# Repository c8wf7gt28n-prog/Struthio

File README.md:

# Graphite 0.8.3 · Kasandra's hologram, her typewriter face for every word, DELETE, burnt yellow and the neon kp

Graphite is a quiet workspace for ideas, research, documents and engineering work, with its AI beside the work. It runs on
one minimal Debian computer (a phone is optional access) and keeps everything on that computer unless you turn a service
on. Graphite is the public name of the workspace; its assistant's face is Stacy (Kasandra in the Kasandra appearance); before November 6, 2026 the program was called Ledger &
Slate, and folders, scripts, settings keys and internal names keep those earlier names for compatibility.

- **From the ThinkPad** · the eight menus (Work, Revise, Tools, Arrange, Commands, Rules, Properties, Guide) stand in the open across the head; one dial sets how strongly the desk glows (Rules ▸ Desk artwork ▸ Glow: Soft, Bright, Neon; it opens on Neon); no key is printed beside the thing it does; the left trees are green circuit traces with the path to the current row lit; the menus' lines carry glyphs.
- **No System menu** · the four meters at the foot are doors: click **CPU** for Graphite's work (what runs and waits, Stop all jobs), **GPU** for Stacy's model and Graphite's services, **RAM** for memory and Machine, **TXT** for the Full chat and what Stacy has in view. Leaving (Log out, Exit Graphite, Restart, Shut down) is at the foot of the **Work** menu; the game is at the foot of **Programs**. The equalizer in the head shows everything that moves (processor, kernel, memory, disks, network, graphics); click it for what each reads. A small control at the left end of the line opens the room above it: one chevron for more, two for taller, one down to close.
- **A start in another program** · say "start a Godot project called Lander" and Stacy makes a folder in Files with the smallest project that runs (project file, one scene, one script) and a page of first steps, written for the Godot on this computer; the Godot room reads it back, and opening it in Godot is a step that waits for you, or is hers with a free hand. One Undo deletes the folder (DELETE gives it back).
- **Stacy's hand** · two words under her face (in Kasandra, on her masthead, after what she speaks with) say how far she acts by herself; click them to change it. **Ask first**: every change waits for your Approve. **Do and show** (what it opens with): a change you ask her for is made at once and shown, with one **Undo** that puts back exactly what it took. **Free hand**: she also makes the changes the records mark for approval and, after a change, brings back to current what stood on it. Say "make a folder called Bracket" or "write a file called plan.txt saying …" and it is in Files as if you had saved it, with an Undo that deletes it (DELETE gives it back). What cannot be undone always asks. Her trail (**What she did…**) lists every act.
- **One line to type on** · five names stand at the left of the line at the bottom: Stacy, Terminal, Search, Web, Log. The lit one gets the words. Web opens an address, or searches for words, in this computer's own browser; with Stacy or Search lit, a line that is only an address (https://…, www.…, localhost) is opened there too, and anything else stays with whom it was typed to. The arrow at the line's end says what it will do, and turns green to run a line that reads.
- **The head and the right pane** · the middle of the head is an equalizer: each bar is one processor thread of this computer over the last second. The right pane is one view, Stacy: her face (in Kasandra, her masthead; her picture stands as a hologram in the left pane's lower part), **This** (what is open or selected), **Now** (what is running and what waits), and the conversation.
- **Simple at rest** · the bar above the work says the name of what is open (click it for its address); tools are drawn glyphs with no boxes; Stacy is the right pane; the name of a thing is said once.
- **The map** · **Z** glides back to show the whole desk, and from that far a sheet is the glyph of its kind, its name in letters that stay readable, and the mark of its state. The Field opens as it was last seen.
- **Find, everywhere** · Find (Ctrl+F) opens one line above the work on whatever is open: writing, the cells of a sheet, a list, the lines of a finding, the words of a PDF page. Enter for the next place, Shift+Enter for the one before, Esc to close.
- **Start here** · [ThinkPad first install](docs/THINKPAD_FIRST_INSTALL.md) covers USB setup, the model-free first launch and the observed hardware.
- **Once** · each action has one visible home (its key is the second road, the right button on a thing is that thing's own road) and a name is said once. Save is lit only when a press would save something.
- **Buttons** · an action is a button (a dark plate with a quiet edge, never a bright outline) and a word that only goes somewhere is underlined, so the interface is never mistaken for the work. A PDF page is shown in the desk's light, its paper brought down from white; its own light is one line away under **More ▾**. The sheet, the PDF and the page of writing each have one row of tools, with what is needed now and then under **More ▾**; the keys at the foot of the Field are buttons.
- **Icons** · every tool is one of Graphite's own drawn glyphs with no box at all; what is particular to a page keeps its words beside its glyph. Work ▸ Rules ▸ Buttons ▸ Words brings back worded plates.
- **The mouse first** · above whatever is open in the centre: **‹ Field**, Find, **−** **+**, Undo, Redo, Save, always in the same place. In the Field **Z** shows the whole desk and the bars at the edges drag; the right button on a sheet shows what can be done with it.
- **Amber** · one amber halo marks where the keys go (the selected sheet, the page being read, or the writing line); what waits for you is lit at its mark, and Approve glows until it is pressed.
- **Green** · the pointer (the mark's two facets, aimed at 11 o'clock) is drawn in the desk's green and carries a little light over the Field; whatever it is over answers in green, and what is live glows. Amber stays for what is selected and what waits for you. The Clean desk keeps the green and drops the glow.
- **The mouse** · click a tile in the Field to open it in the centre; **‹ Field** above the centre comes back to the same tile; the buttons at the foot of the Field do what their keys do; a change that waits has an **Approve** button. Ask Stacy "set B3 to 300" and, with her hand at Do and show, it is done at once with an Undo; at Ask first it waits for your Approve with what it would move marked.
- **Every key** · press **?** in the Field for a card of every key. The doubt (X), the desk check (C) and the brief (B) open on a page over the work at your reading size; the doubt and the check step aside at the next key.
- **Look ahead** · with a sheet or a calculation selected in the Field, ask "what if B4 were 100?": the cell is set without changing anything, the wires are followed, and the Field marks everything that would move with what it would say (**Esc** clears).
- **The brief** · press **B** in the Field: the whole desk written up as one page, from the records and by no model; **G** keeps it as a page that knows when the desk has moved on.
- **Right-click** · on a sheet in the Field the menu cascades: What if › a number › a value to try; Doubt it › what Stacy finds, each row opening its evidence; Trace it › every step back and on; What can be done › the steps; Your words ›.
- **Your own words** · `word waits = field.read | pick waiting | select kind,title,state`, then `waits`, `waits | count`, `words`, `forget waits`: a line kept under a word of yours.
- **Doubt** · press **X** on a sheet in the Field: Stacy cross-examines it for what a plausible result may hide (an edited input, mixed conditions, one source, a check that cannot fail, a number recorded nowhere) and **D** offers the step that removes the doubt.
- **A line reads the desk** · `field.read | pick waiting | select kind,title,state`; `this` is the sheet selected in the Field; **T** traces a thing to its source; ask "what if B3 were 320?" about a calculation and nothing is changed.
- **Doing** · press **D** on a sheet in the Field for the steps the records offer (a read runs; a change that waits is marked "asks first" and waits for **G**, your go; with Stacy's hand at Do and show or Free hand, the others are done when you take them); **C** checks the desk and offers to settle what needs no decision of yours.
- **The shelf** · press **P** in the Field: every program and room in six fixed columns; Enter opens one.
- **The Field** · press **F9** (or Arrange → Field, or type `field` in the writing strip): the work in this workspace as sheets with the wires that say what feeds what. Arrow keys follow the wires, Enter opens the real page, Esc comes back. Stacy's rail shows the line that reads the selected sheet: **S** puts it in the writing strip, **Shift+Enter** runs it. **N** shows this computer's network the same way; **W** returns to the work. It is the first slice of the objects and instruments desktop (master specification, sections 70 to 72), new in 0.3. Right-click a sheet (or press the Menu key) for what can be done with it. Guide → What's New has the rest.
- **Visual baseline** · [Visual Pass 1 reference review](docs/BOSS_VISUAL_PASS_01_REVISION.md) compares the five owner references with the revised worksheet, PDF evidence review and research journal.
- **Halfway release** · [P08–P10](docs/BOSS_HALFWAY_P10.md) covers resident model handling, project collections and reviewed PDF tables that become sheets and reports.
- **Evidence preparation** · [Intelligent data arrangement P07](docs/INTELLIGENT_DATA_P07.md) covers source preparation, exact calculations and follow-up passages.
- **Resource scheduling** · [Traffic cop P06](docs/TRAFFIC_COP_P06.md) covers shared-memory admission, foreground turns and readable waiting reasons.
- **Hardware route:** read [ThinkPad / Vulkan P05](docs/THINKPAD_VULKAN_P05.md): the bundled Vulkan worker, hardware profile, launch defaults, actual backend readback and CPU fallback.
- **Current desk:** read [BOSS M1](docs/BOSS_M1.md): the new native interface, path, contextual commands and constructed chains.
- **Earlier guide:** read [the daily guide](docs/DAILY_GUIDE.md) (the desk, the programs list, the four meters and leaving, the
  writing line and its four modes, Log with its Events and Network streams, the right-click menu, documents, assignments, the
  Finder, Ingress and Egress, the local model, the game behind the mark).
- **Working on it:** read [RECORD_OF_DIRECTIONS.md](RECORD_OF_DIRECTIONS.md) first: the owner's directions, where the
  knowledge is, where things stand and how to continue.

The supplied Graphite 0.1 baseline has historical mechanical and offscreen evidence from the build container, and live trials of the small Qwen models
where the docs say so. The owner reports (13 November 2026) that 0.4.6 is installed and running on the ThinkPad; no account of what was tried
there is recorded yet, nothing later has run there, and the owner's model file has not been tried. Nothing here claims
any of it is accepted.

The BOSS upgrade implements P01–P10 of the twenty-pass campaign. Try **References → Read technical PDF → Review table** to make a sheet from a reviewed source. Open **Project Desk → Ask Stacy → Prepare evidence** to see matching project passages and exact results before a model turn. Live model and owner-host Vulkan qualification remain pending. P11 covers full native programs.

## Install

From the release volumes (`Graphite_0.8.3_part_NN.zip`, `RELEASE_PARTS.json` and `INSTALL_LS.py` in one folder, for
example a USB stick), as your ordinary Debian user:

```
python3 INSTALL_LS.py --usb . --target "$HOME/Applications/Graphite-0.8.3" --minimal-session --vulkan --plan
python3 INSTALL_LS.py --usb . --target "$HOME/Applications/Graphite-0.8.3" --minimal-session --vulkan --yes
```

`INSTALL_LS.py` is the Graphite installer (its file name is kept: scripts, tests and earlier notes call it). It verifies
every volume, restores the program into a new folder, installs the Debian prerequisites (with `--yes`, through sudo) and
the pinned Python dependencies, checks the runtime imports, the payload and the seed, and ends with one line that says
what actually happened. `--extract-only` verifies and restores without installing anything; `--offline` uses a prepared
cache only; `--public-manifest URL --manifest-sha256 HASH` installs from a published release. Every option and refusal is
explained in [docs/MINIMAL_DEBIAN_INSTALL_01.md](docs/MINIMAL_DEBIAN_INSTALL_01.md).

From an already extracted program folder:

```
bash INSTALL_DEBIAN.sh --quick            # asks before sudo; add --vulkan for Radeon dependencies, --minimal-session for the dedicated session, or other tool options as needed
bash INSTALL_LEDGER.sh --quick            # the runtime only, on a system that already has the prerequisites
```

Keep your previous program folder and every workspace; install a new release into a new folder. A local model is
optional: the daily guide says which small GGUF file to fetch and how to register it in the Brain room. No model file is
included.

## Start

```
bash START_MINIMAL_DEBIAN.sh   # from a Debian text login: the dedicated fullscreen session; prints "Graphite ended with status N" when you leave
bash START_OFFICE.sh           # from an existing desktop: the ordinary window on the Office workspace (~/Concern/Office)
```

Leave through the Work menu's last group → Return to Debian, or Exit Graphite on an
existing desktop. The same group's Log out, Restart and Shut down first save or set aside your work as leaving does, ask you
to confirm, and then ask the system's own logind (never sudo); without a login session they say they are unavailable. On Windows, `START_OFFICE.cmd` starts the same program after Python
and `requirements-qt.txt` are installed.

## Operator tools

```
bash LEDGER.sh doctor                 # inspects the installation; creates no workspace, starts nothing
bash LEDGER.sh doctor --self-test     # a disposable capture, restart, backup and restore round trip
bash LEDGER.sh doctor --qt-check      # the real window and capture widget, offscreen
bash LEDGER.sh baseline --out my-baseline.json
bash LEDGER.sh inventory
```

## Complete backups

Close Graphite before taking a backup. This includes ordinary workspace files and working copies; restore always writes
NEW folders and leaves existing work untouched:

```
bash LEDGER.sh backup create --root ~/Concern/Office --out ~/Graphite-backups/office
bash LEDGER.sh backup verify ~/Graphite-backups/office
bash LEDGER.sh backup restore ~/Graphite-backups/office --to ~/Concern/Office-restored
bash LEDGER.sh open --root ~/Concern/Office-restored --profile ~/Concern/Office-restored-profile
```

External originals and external model weights are not included; model files inside the workspace are left out unless
`--include-models` is given. Complete snapshots and no-replace publication target Linux. docs/STAGE1.md explains backup and
restore in full.

## Checks

```
python3 tools/check_release.py               # payload, seed and syntax; the live program against docs/GRAPHITE_0.1_REGISTRY.json; the privacy scan
python3 tools/check_release.py --self-test   # adds the focused tests_integrated modules, one module per child process
python3 tools/check_release.py --ui          # adds the offscreen Qt checks of the UI gate
python3 -m workbench.slate_checks --runtime
python3 -m workbench.continuing_checks --workers
python3 -m workbench.deployment_checks --ui
```

`tools/check_release.py` is the one entry for the release check (it runs `tools/check_hatch.py`). The registry record
`docs/GRAPHITE_0.1_REGISTRY.json` holds every operation's scope and argument-schema digest, the job tools, every setting
definition's digest and the adapters; `tools/record_registry.py` writes it from the live tree, and any difference is listed
in words. It submits no job, starts no model or worker, makes no provider request and invokes no native tool. A passing
check is integrity, not readiness or acceptance. Tests run one module at a time:
`python3 -B -m unittest tests_integrated.test_graphite` (tests_integrated has no `__init__.py`; do not use discover).

## Paired exchange, signed releases and deployment

Arrange → Exchange & deployment holds recipient-bound request and result pills, pinned mutual TLS 1.3, replay protection,
explicit signed offline release verification and recovery, reviewable launch files and optional read-only phone progress.
A received pill stays in quarantine until explicitly accepted; returned edits become a frozen working-copy proposal, and
originals still need separate owner publication. Nothing starts merely by opening the panel. Read docs/STAGE6.md before
pairing or updating. No publisher private key or default trust root is included.

## Packaging

```
python3 tools/package_graphite.py --dry-run                                     # what would be shipped; writes nothing
python3 tools/package_graphite.py OUT
python3 tools/package_release_parts.py OUT/Graphite_0.8.3_full.zip PARTS "Graphite 0.8.3"
```

Graphite's own code and documents are free software under the GNU General Public License, version 2 only (COPYING).
Stacy's artwork, the other project art, the names and the game copy are kept back (RIGHTS.md). Licences of bundled fonts,
runtimes and dependencies are in THIRD_PARTY_NOTICES.md; the pinned dependencies are the requirements-*.txt files.

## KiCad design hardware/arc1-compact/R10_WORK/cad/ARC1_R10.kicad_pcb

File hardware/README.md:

# Hardware

`arc1-compact/` is the ARC-1 Compact console hardware handoff: the owner-issued R06 directive,
the unchanged R05 baseline, and the R06 engineering work. Start with
`arc1-compact/START_HERE.md`, then read `arc1-compact/R06_WORK/STATUS_PASS6.md`. Nothing under
this directory is part of the STRUTHIO web build.

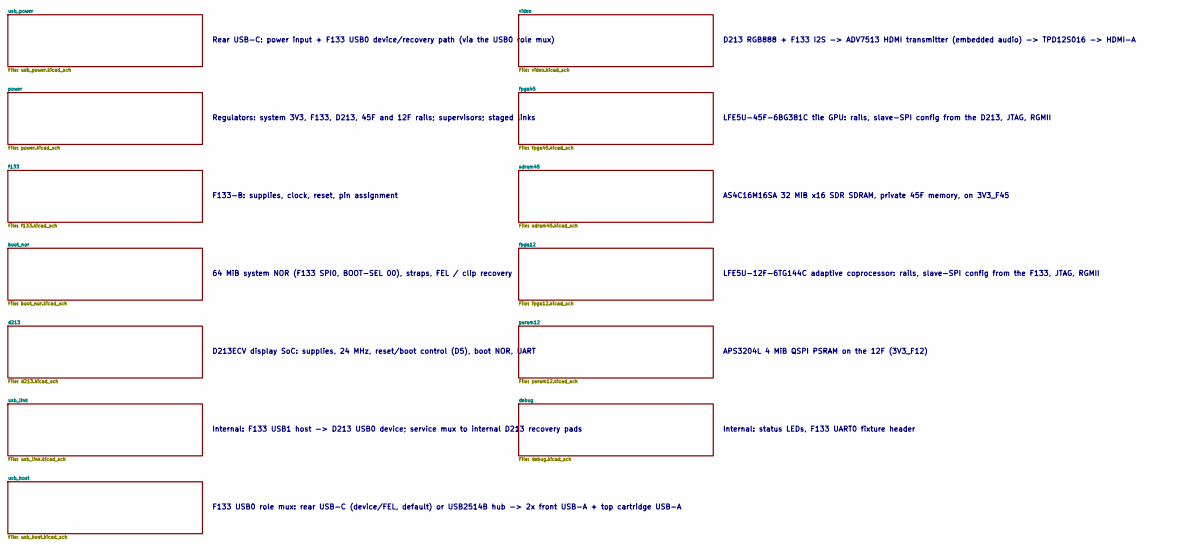
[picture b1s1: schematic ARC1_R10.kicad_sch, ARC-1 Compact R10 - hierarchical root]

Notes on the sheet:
Rear USB-C: power input + F133 USB0 device/recovery path (via the USB0 role mux)
Regulators: system 3V3, F133, D213, 45F and 12F rails; supervisors; staged links
F133-B: supplies, clock, reset, pin assignment
64 MiB system NOR (F133 SPI0, BOOT-SEL 00), straps, FEL / clip recovery
D213ECV display SoC: supplies, 24 MHz, reset/boot control (D5), boot NOR, UART
Internal: F133 USB1 host -> D213 USB0 device; service mux to internal D213 recovery pads
F133 USB0 role mux: rear USB-C (device/FEL, default) or USB2514B hub -> 2x front USB-A + top cartridge USB-A
D213 RGB888 + F133 I2S -> ADV7513 HDMI transmitter (embedded audio) -> TPD12S016 -> HDMI-A
LFE5U-45F-6BG381C tile GPU: rails, slave-SPI config from the D213, JTAG, RGMII
AS4C16M16SA 32 MiB x16 SDR SDRAM, private 45F memory, on 3V3_F45
LFE5U-12F-6TG144C adaptive coprocessor: rails, slave-SPI config from the F133, JTAG, RGMII
APS3204L 4 MiB QSPI PSRAM on the 12F (3V3_F12)
Internal: status LEDs, F133 UART0 fixture header

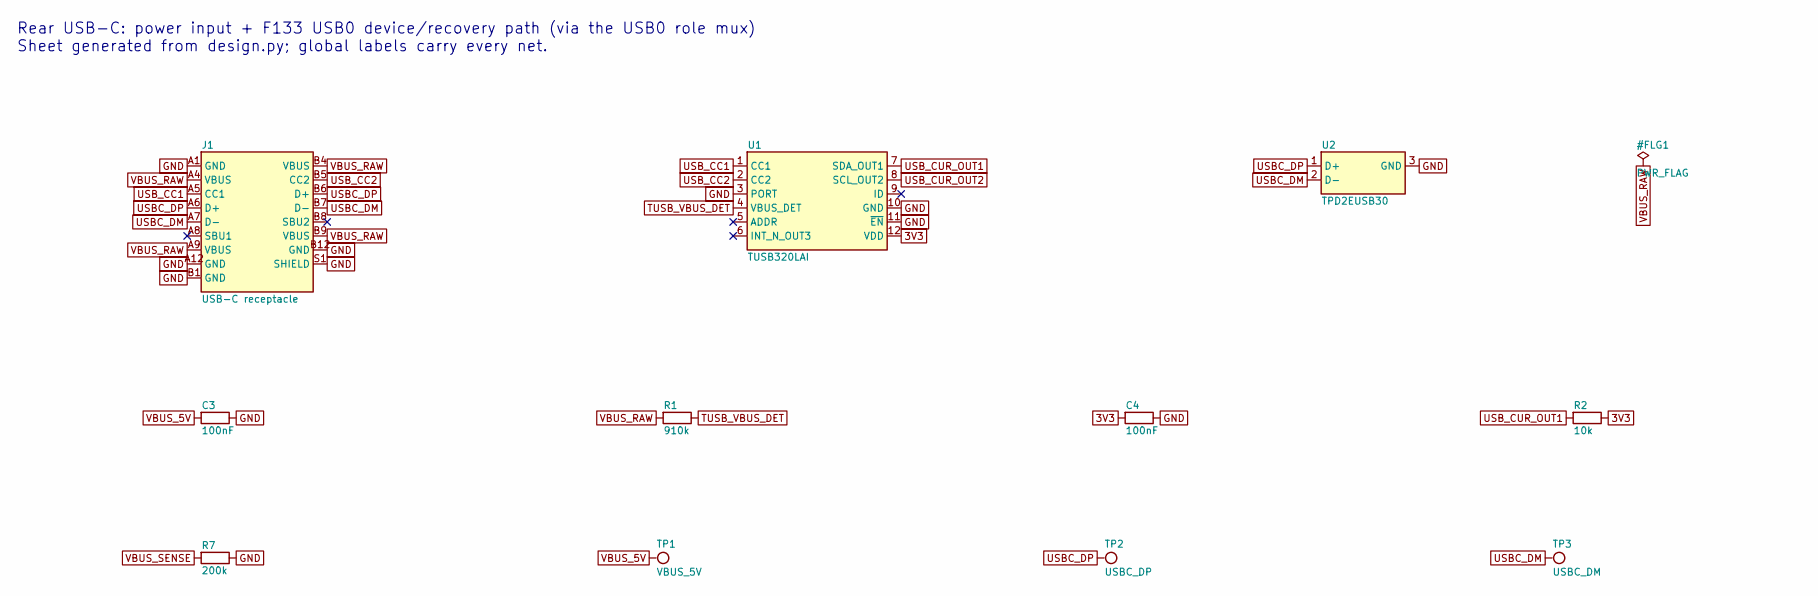
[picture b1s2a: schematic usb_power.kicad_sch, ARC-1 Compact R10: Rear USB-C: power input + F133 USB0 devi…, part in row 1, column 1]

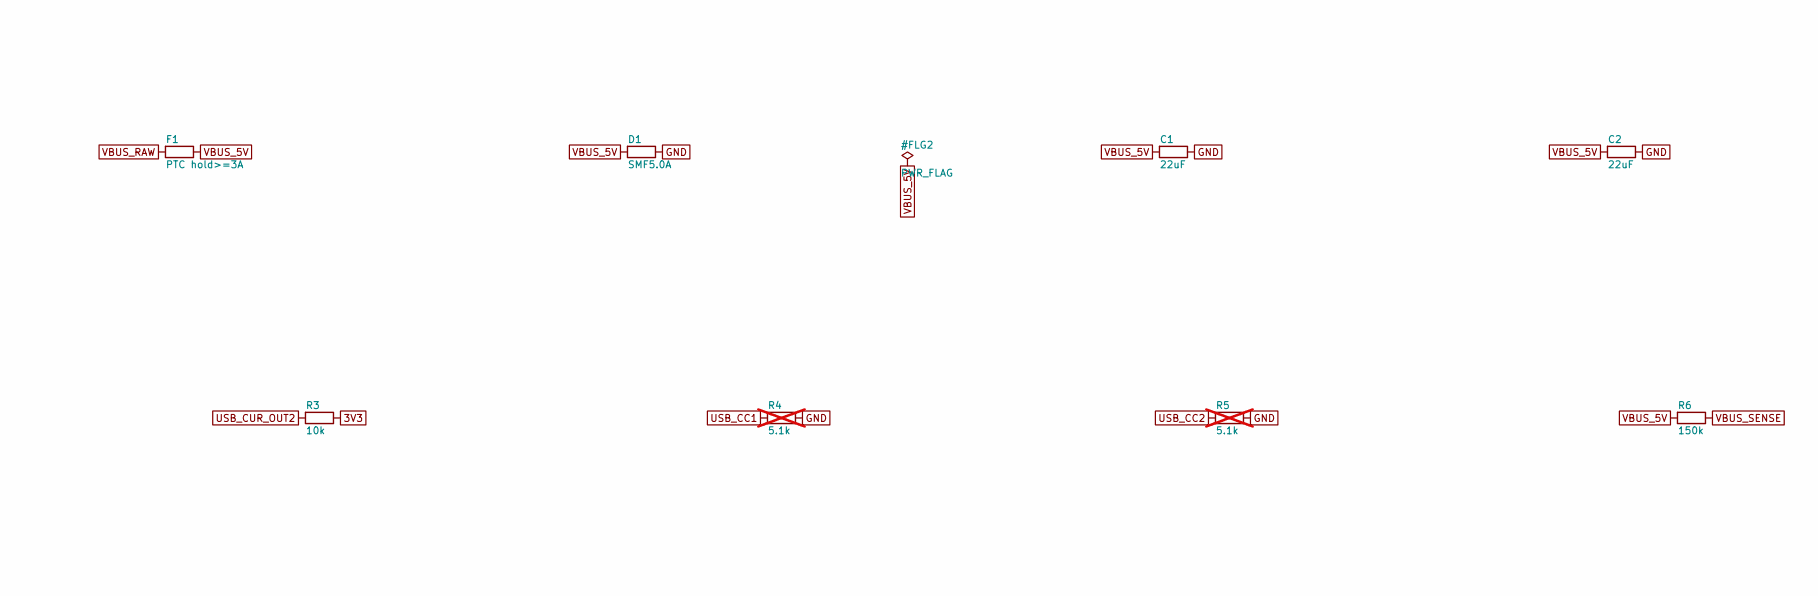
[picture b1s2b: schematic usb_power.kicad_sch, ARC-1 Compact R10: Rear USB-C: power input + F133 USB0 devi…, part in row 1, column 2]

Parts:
C1, C2: 22uF; C_0805_2012Metric; MPN CL21A226MQQNNNE; LCSC C5674
C3, C4: 100nF; C_0402_1005Metric; MPN CL05B104KO5NNNC; LCSC C1525
D1: SMF5.0A; D_SMF; MPN SMF5.0A
F1: PTC hold>=3A; Fuse_1812_4532Metric; MPN TBD (1812 PTC, hold >= 3 A, 6 V)
J1: USB-C receptacle; USB_C_Receptacle_GCT_USB4105-xx-A_16P_TopMnt_Horizontal; MPN USB4105-GF-A; LCSC C5184243
R1: 910k; R_0402_1005Metric
R2, R3: 10k; R_0402_1005Metric; MPN 0402WGF1002TCE; LCSC C25744
R4, R5: 5.1k; R_0402_1005Metric; not fitted
R6: 150k; R_0402_1005Metric
R7: 200k; R_0402_1005Metric
TP1: VBUS_5V; TestPoint_Pad_D1.0mm
TP2: USBC_DP; TestPoint_Pad_D1.0mm
TP3: USBC_DM; TestPoint_Pad_D1.0mm
U1: TUSB320LAI; SLIM4_FP_U13_TUSB320LAI_RWB_X2QFN12; MPN TUSB320LAIRWBR; LCSC C132554
U2: TPD2EUSB30; SLIM4_FP_U11_TPD2EUSB30_DRT3; MPN TPD2EUSB30DRTR; LCSC C97502

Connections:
3V3: C4.1, R2.2, R3.2, U1.12 (VDD); also elsewhere on the board
GND: C1.2, C2.2, C3.2, C4.2, D1.2 (A), J1.A1 (GND), J1.A12 (GND), J1.B1 (GND), J1.B12 (GND), J1.S1 (SHIELD), R4.2, R5.2, R7.2, U1.3 (PORT), U1.10 (GND), U1.11 (~EN), U2.3 (GND); also elsewhere on the board
TUSB_VBUS_DET: R1.2, U1.4 (VBUS_DET)
USBC_DM: J1.A7 (D-), J1.B7 (D-), TP3.1, U2.2 (D-); also elsewhere on the board
USBC_DP: J1.A6 (D+), J1.B6 (D+), TP2.1, U2.1 (D+); also elsewhere on the board
USB_CC1: J1.A5 (CC1), R4.1, U1.1 (CC1)
USB_CC2: J1.B5 (CC2), R5.1, U1.2 (CC2)
USB_CUR_OUT1: R2.1, U1.7 (SDA_OUT1); also elsewhere on the board
USB_CUR_OUT2: R3.1, U1.8 (SCL_OUT2); also elsewhere on the board
VBUS_5V: C1.1, C2.1, C3.1, D1.1 (K), F1.2, R6.1, TP1.1; also elsewhere on the board
VBUS_RAW: F1.1, J1.A4 (VBUS), J1.A9 (VBUS), J1.B4 (VBUS), J1.B9 (VBUS), R1.1
VBUS_SENSE: R6.2, R7.1; also elsewhere on the board

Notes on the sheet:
Rear USB-C: power input + F133 USB0 device/recovery path (via the USB0 role mux) Sheet generated from design.py; global labels carry every net.
